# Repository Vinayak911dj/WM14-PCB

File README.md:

This is ReadMe for WM14 PCB
It is a KiCAD file contailes Schematic and PCB Design. it has PDF and Gerber files

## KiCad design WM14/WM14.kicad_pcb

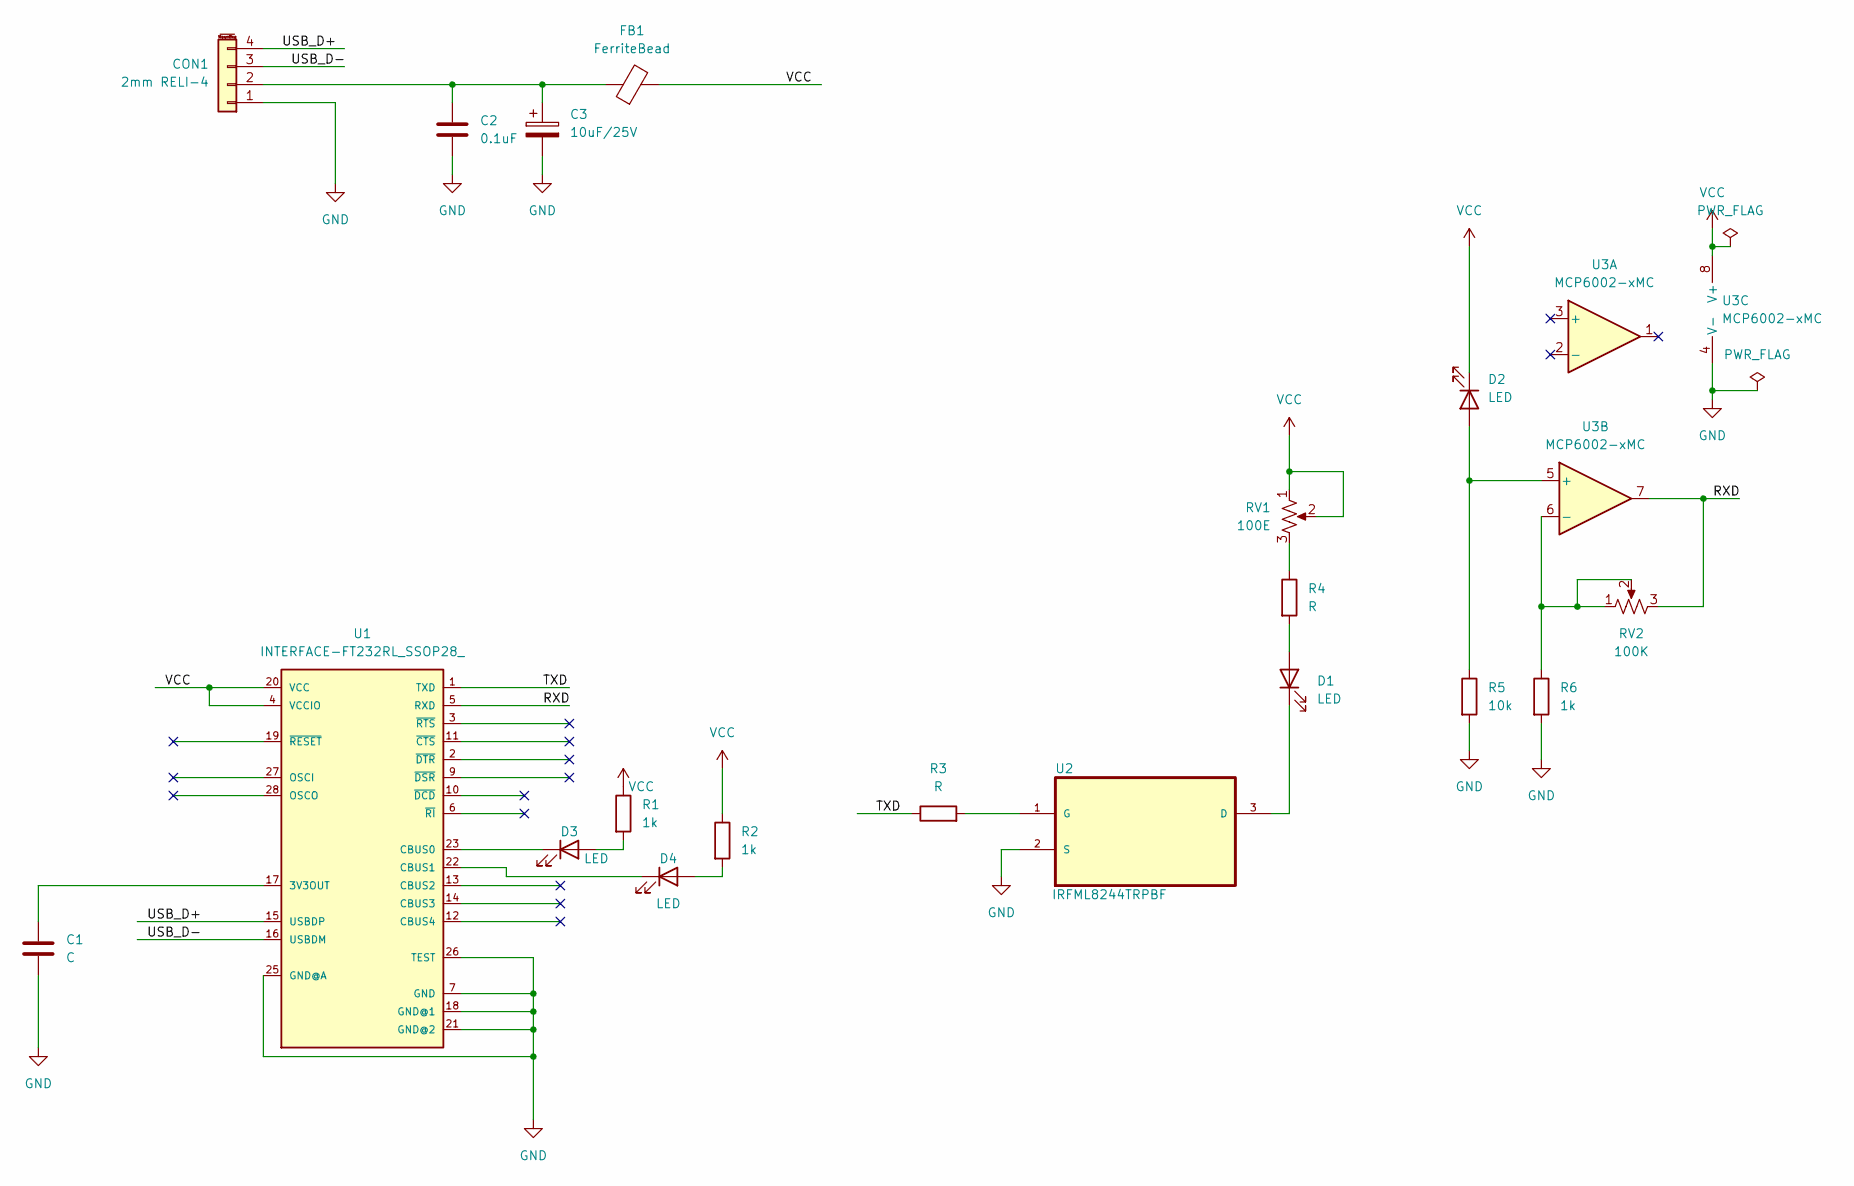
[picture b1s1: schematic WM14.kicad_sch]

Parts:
C1: C; C_0805_2012Metric
C2: 0.1uF; C_0805_2012Metric
C3: 10uF/25V; C_0805_2012Metric
CON1: 2mm RELI-4; PinSocket_1x04_P2.00mm_Vertical
D1, D2: LED; LED_D5.0mm_Clear
D3, D4: LED; LED_0805_2012Metric
FB1: FerriteBead; L_0805_2012Metric
R1, R2, R6: 1k; R_0805_2012Metric
R3, R4: R; R_0805_2012Metric
R5: 10k; R_0805_2012Metric
RV1: 100E; Potentiometer_Bourns_3314R-1_Vertical_Hole
RV2: 100K; Potentiometer_Bourns_3314R-1_Vertical_Hole
U1: INTERFACE-FT232RL_SSOP28_; SSOP28-0.65-10.2X5.2MM; MPN FT232RL
U2: IRFML8244TRPBF; SOT95P240X112-3N; MPN IRFML8244TRPBF
U3: MCP6002-xMC; DFN-8-1EP_3x2mm_P0.5mm_EP1.75x1.45mm

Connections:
/RXD: RV2.3, U1.5 (RXD), U3.7
/TXD: R3.1, U1.1 (TXD)
/USB_D+: CON1.4, U1.15 (USBDP)
/USB_D-: CON1.3, U1.16 (USBDM)
GND: C1.2, C2.2, C3.2, CON1.1, R5.2, R6.2, U1.7 (GND), U1.18 (GND@1), U1.21 (GND@2), U1.25 (GND@A), U1.26 (TEST), U2.2 (S), U3.4 (V-), U3.9 (V-)
unnamed: C2.1, C3.1, CON1.2, FB1.1
unnamed: D1.2 (A), R4.2
unnamed: D1.1 (K), U2.3 (D)
unnamed: D2.2 (A), R5.1, U3.5 (+)
unnamed: D3.2 (A), R1.2
unnamed: D3.1 (K), U1.23 (CBUS0)
unnamed: D4.2 (A), R2.2
unnamed: D4.1 (K), U1.22 (CBUS1)
unnamed: R4.1, RV1.3
unnamed: C1.1, U1.17 (3V3OUT)
unnamed: R3.2, U2.1 (G)
unnamed: R6.1, RV2.1, RV2.2, U3.6 (-)
VCC: D2.1 (K), FB1.2, R1.1, R2.1, RV1.1, RV1.2, U1.4 (VCCIO), U1.20 (VCC), U3.8 (V+)

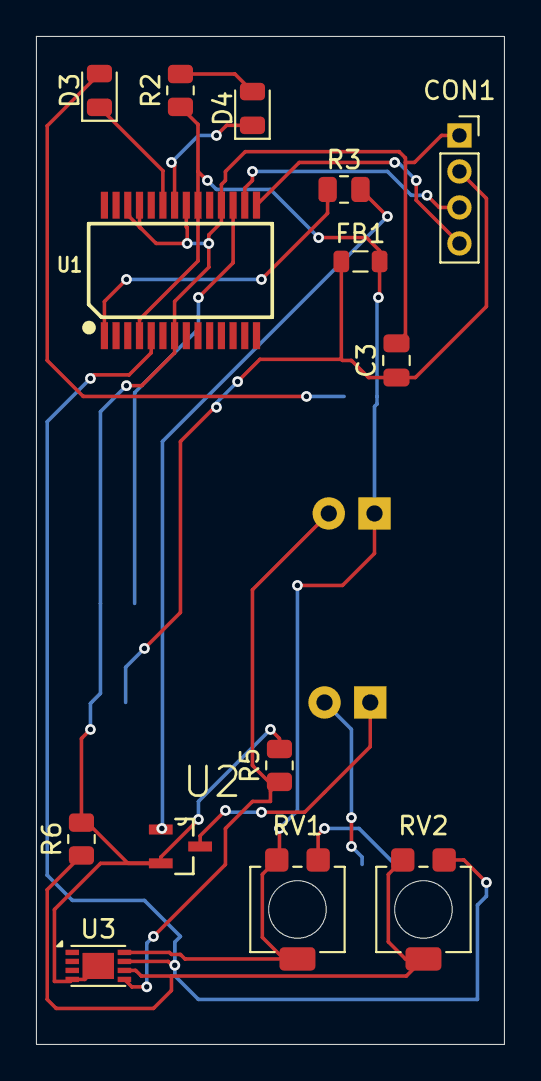
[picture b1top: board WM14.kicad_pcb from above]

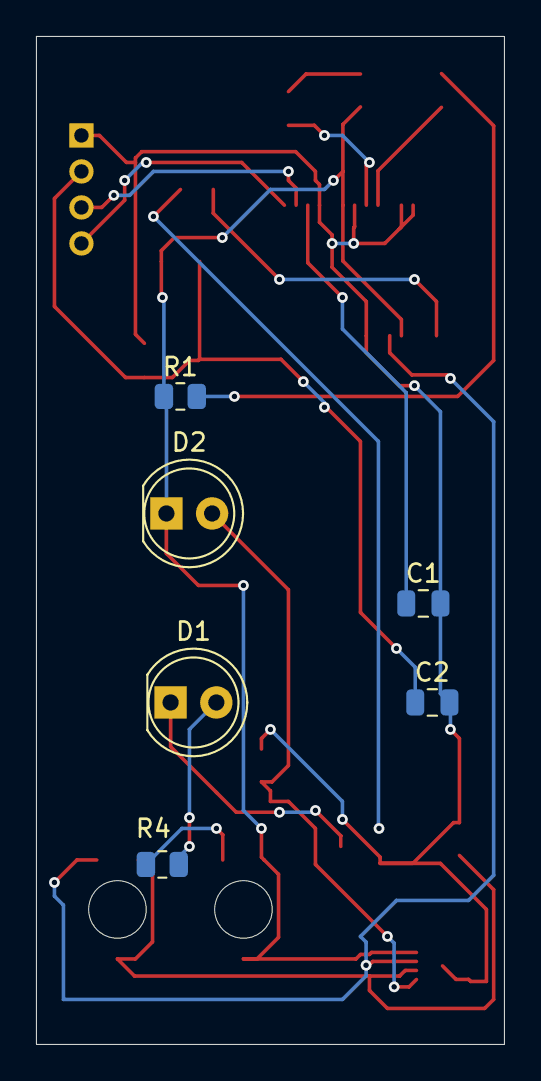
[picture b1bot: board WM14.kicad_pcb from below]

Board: 2 copper layers, 26.0 x 56.0 mm, 20 parts (6 on the bottom side), 18 nets.

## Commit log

2024-06-26 PCB file of Water Meter 14
